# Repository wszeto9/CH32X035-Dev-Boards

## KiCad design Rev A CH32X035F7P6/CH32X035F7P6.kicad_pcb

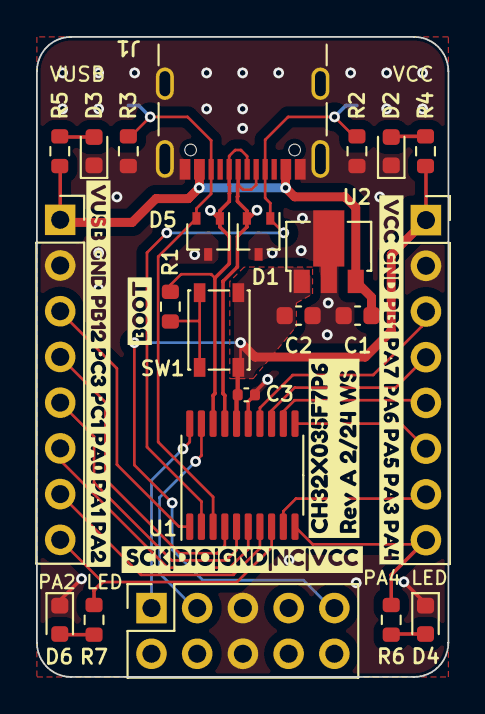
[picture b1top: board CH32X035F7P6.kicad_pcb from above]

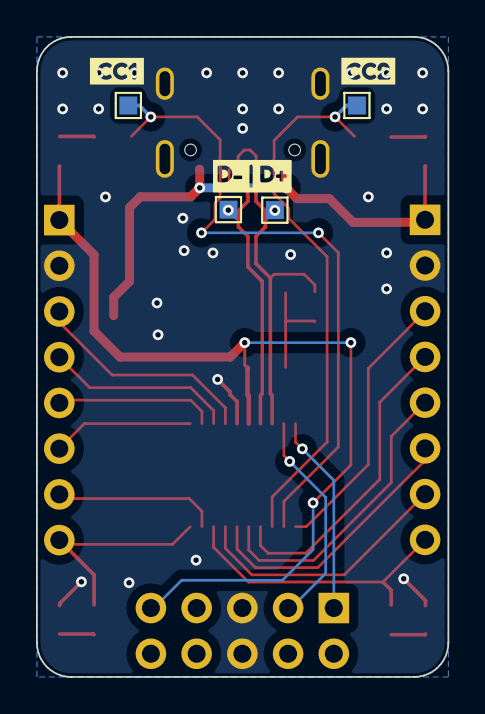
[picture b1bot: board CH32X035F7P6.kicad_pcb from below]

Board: 2 copper layers, 22.9 x 35.6 mm, 35 parts (7 on the bottom side), 26 nets.

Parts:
C1: 0603,1uF,50V,X5R; C_0603_1608Metric
C2: 0603,100nF,50V,X7R; C_0603_1608Metric
C3: 0402,100nF,16V,X7R; C_0402_1005Metric
D1, D5: SP0502BAJT; SOT-323_SC-70
D2, D3, D4, D6: LED_White; LED_0603_1608Metric
J1: USB4105; USB_C_Receptacle_GCT_USB4105-xx-A_16P_TopMnt_Horizontal
J2: Conn_02x05_Odd_Even; PinSocket_2x05_P2.54mm_Vertical
J3, J4: Conn_01x08_Socket; PinSocket_1x08_P2.54mm_Vertical
R1: 0603,4.7k; R_0603_1608Metric
R2, R3: 0603,5.1k; R_0603_1608Metric
R4, R5, R6, R7: 0603,1k; R_0603_1608Metric
SW1: PTS810 SJM; SW_SPST_PTS810
TP1, TP2, TP3, TP4: TestPoint; TestPoint_Pad_1.0x1.0mm
U1: CH32X035F7P6; TSSOP-20_4.4x6.5mm_P0.65mm
U2: L78L05_SOT89; SOT-89-3
kibuzzard-65CC39B9: G***; kibuzzard-65CC39B9
kibuzzard-65CC43B3: G***; kibuzzard-65CC43B3
kibuzzard-65CC43C3: G***; kibuzzard-65CC43C3
kibuzzard-65CC43E3: G***; kibuzzard-65CC43E3
kibuzzard-65CC414F: G***; kibuzzard-65CC414F
kibuzzard-65CC468F: G***; kibuzzard-65CC468F
kibuzzard-65CC3977: G***; kibuzzard-65CC3977
kibuzzard-65CC4705: G***; kibuzzard-65CC4705

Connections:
/CC1: D1.1 (K), J1.A5 (CC1), R2.2, TP3.1, U1.2 (PC14/CC1)
/CC2: D5.2 (K), J1.B5 (CC2), R3.2, TP4.1, U1.3 (PC15/CC2)
/PA0: J4.6, U1.6 (PA0)
/PA1: J4.7, U1.7 (PA1)
/PA2: J4.8, R7.1, U1.8 (PA2)
/PA3: J3.7, U1.9 (PA3)
/PA4: J3.8, R6.1, U1.10 (PA4)
/PA5: J3.6, U1.11 (PA5)
/PA6: J3.5, U1.12 (PA6)
/PA7: J3.4, U1.13 (PA7)
/PB1: J3.3, U1.14 (PB1)
/PB12: J4.3, U1.1 (PB12)
/PC1: J4.5, U1.5 (PC1)
/PC3: J4.4, U1.4 (PC3)
/SWDCLK: J2.1, U1.20 (PC19/DCK)
/SWDIO: J2.3, U1.19 (PC18/DIO)
/USB_CH32_N: D1.2 (K), J1.A7 (D-), J1.B7 (D-), TP1.1, U1.17 (PC16/UDM)
/USB_CH32_P: D5.1 (K), J1.A6 (D+), J1.B6 (D+), R1.1, TP2.1, U1.18 (PC17/UDP)
/VCC_CH32: C2.1, C3.1, J2.9, J3.1, R4.1, SW1.1 (A), U1.16 (VDD), U2.1 (OUT)
/VUSBC: C1.1, J1.A4 (VBUS), J1.A9 (VBUS), J1.B4 (VBUS), J1.B9 (VBUS), J4.1, R5.1, U2.3 (IN)
GND: C1.2, C2.2, C3.2, D1.3 (A), D2.1 (K), D3.1 (K), D4.1 (K), D5.3 (A), D6.1 (K), J1.A1 (GND), J1.A12 (GND), J1.B1 (GND), J1.B12 (GND), J1.S1 (SHIELD), J2.5, J2.6, J3.2, J4.2, R2.1, R3.1, U1.15 (GND), U2.2 (GND)
unnamed: D2.2 (A), R4.2
unnamed: D3.2 (A), R5.2
unnamed: D4.2 (A), R6.2
unnamed: D6.2 (A), R7.2
unnamed: R1.2, SW1.2 (B)

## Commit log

2024-02-14 Laid out rev A
